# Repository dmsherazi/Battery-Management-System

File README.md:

Battery Management System
-------------------------

This project provides software for monitoring, control and charging of batteries
for a solar powered installation.

The motivation to build this arose from the poor performance, lack of
adequate control, lack of configuration for different battery types, and poor
user interface of commercially available BMS, at least for those reasonably
priced.

The system allows for up to three batteries to be managed separately. This
ensures that failed batteries may be isolated without adversely affecting the
other batteries, as could happen if batteries were connected in parallel. Also
note that if batteries were connected in parallel, the same type and age of
battery must be used, which would necessitate changing all batteries if one were
to fail.

The system also allows for up to two loads so that critical low current loads
may be kept running after high current loads are disconnected in the event
that all batteries fall to critically low charge levels.

The system uses several methods of tracking the State of Charge of each battery,
This is a notoriously difficult parameter to estimate. In a system with three
batteries one may be isolated long enough to allow the terminal voltage to
settle to a level that will allow SoC to be computed accurately.

In the long term it is intended to allow a variety of configurations for
charging and monitoring of batteries:

1. The common three phase charger is provided using PWM to reduce the voltage
   in the absorption phase. In float phase the charger is disconnected until the
   terminal voltage drops to a threshold value. Equalization is not provided.

2. An algorithm based on Interrupted Charge Control (ICC) is also provided to
   place batteries in rest when they have reached the gassing voltage and there
   are other batteries to be charged. This has advantages of:
   (a) better utilization of the charger among the batteries,
   (b) low EMI,
   (c) reduced gas generation.

A wide range of state information is stored on a removable memory, and also
transmitted over a serial link to allow a GUI to display the state accurately
and in detail.

A GUI is provided to allow control and observation of operations. The GUI has
been provided also on a BeagleBone Black card with a LCD touchscreen. This
is suitable for wall installation and draws very low power. For wireless
communications, XBees placed in point-point AT serial mode were successful.

Each of the six interfaces has a hardware overcurrent circuit breaker and low
voltage detector, as well as providing current and voltage measurements.

A central controller based on STM32F103 controls all interfaces and the MOSFET
switches directly. Hardware signals for overcurrent and low voltage are applied
directly to the MOSFET switches for rapid disconnect.

A data processing program is also provided to generate reports of various types
from the recorded performance data.

More information is available on:

http://www.jiggerjuice.info/electronics/projects/solarbms/solarbms-overview.html

(c) K. Sarkies 12/09/2015

TODO

1. Improvement of MOSFET switch drivers to reduce EMI at higher rates.
2. MPPT regulator for the panel.

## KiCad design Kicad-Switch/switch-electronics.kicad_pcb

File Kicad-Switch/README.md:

Battery Management System Switch
--------------------------------

PCB for the MOSFET switch matrix.

Digital circuitry ensures that no two batteries are connected together, which
could cause damage if the state of charge differs significantly.

A diode matrix is used to provide power for the electronics. It ensures that
power is taken from the loads, or from the batteries if the loads are not
connected. This enables the firmware to keep track of the current drawn by
the local electronics.

The MOSFETs are driven by simple BJT-resistor drivers. This results in quite
slow switching speeds. There may be a need for faster switching e.g. high speed
PWM to reduce EMI. In this case the circuit needs to be modified to use better
drivers.

There were several errors in the circuit, which have been corrected but not
tested. The board is to be replaced with the gEDA version.

In the board, load 1 is the central row of switches and the upper power
connector. Load 2 is the lower row of switches and the lower power connector.
This is the reverse of that used in the interconnect board and has been changed
in the gEDA board.

(c) K. Sarkies 26/04/2014

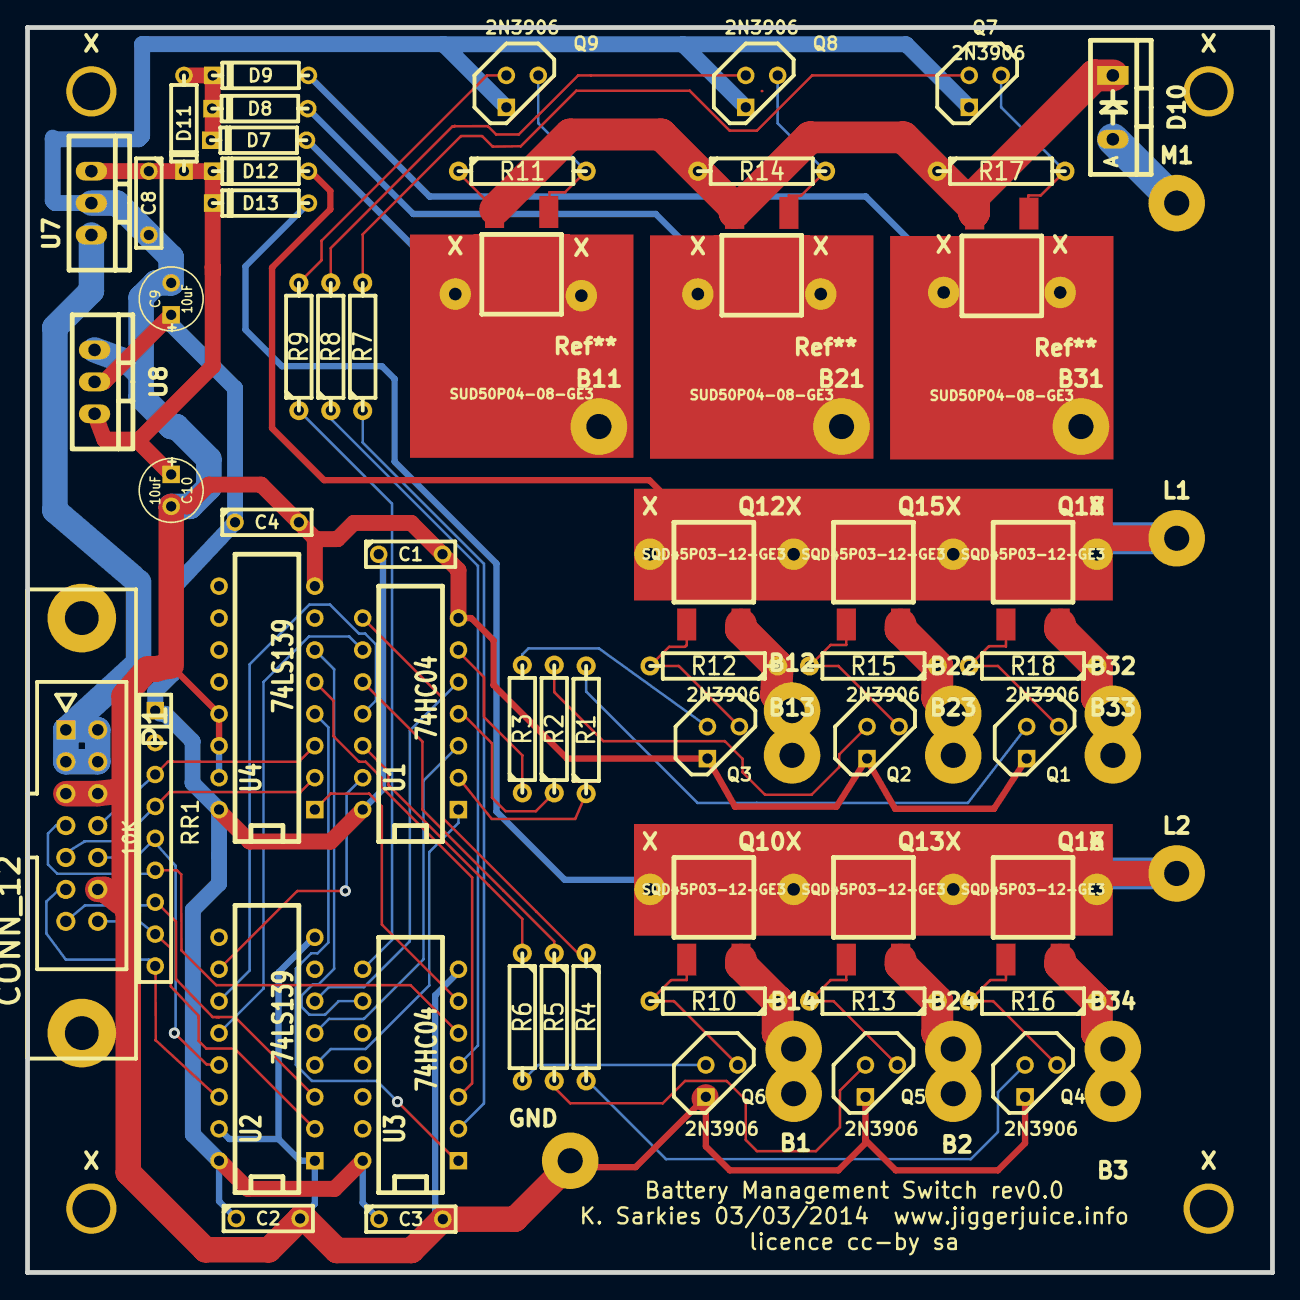
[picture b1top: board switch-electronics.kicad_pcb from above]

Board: 2 copper layers, 99.1 x 99.1 mm, 95 parts (0 on the bottom side), 59 nets.

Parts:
B1, B2, B3, B11, B12, B13, B14, B21, B22, B23, B24, B31, B32, B33, B34: CONN_1; SolderWirePad_single_2mmDrill
C1, C2, C3, C4, C8: 0.1uF; C2
C9, C10: 10uF; C1V5
D7, D8, D9, D11: 1N4701; D3
D10: MBR1645; Diode_TO-220_Vertical
D12, D13: 1N5819; D3
GND: CONN_1; SolderWirePad_single_2mmDrill
L1, L2: CONN_1; SolderWirePad_single_2mmDrill
M1: CONN_1; SolderWirePad_single_2mmDrill
P1: CONN_12; he10-14d
Q1, Q2, Q3, Q4, Q5, Q6, Q7, Q8, Q9: 2N3906; TO92-CBE
Q10, Q12, Q13, Q15, Q16, Q18: SQD45P03-12-GE3; TO252-HS-S
R1, R2, R3, R4, R5, R6, R7, R8, R9: 10K; R4
R10, R11, R12, R13, R14, R15, R16, R17, R18: 1K; R4
RR1: 10K; r_pack8
Ref**: SUD50P04-08-GE3; TO252-HS
Ref**#2, Ref**#3: SUD50P04-08-GE3; TO252-HS
U1, U3: 74HC04; DIP-14__300
U2, U4: 74LS139; DIP-16__300
U7: LM7809CT; TO-220_Neutral123_Vertical
U8: LM1084IT-3.3/NOPB; TO-220_Neutral123_Vertical
X: SolderWirePad_single_2mmDrill
X#2, X#3, X#4: SolderWirePad_single_2mmDrill
X#5, X#6, X#7, X#8, X#9, X#10, X#11, X#12, X#13, X#14, X#15, X#16, X#17, X#18: SolderWirePad_single_1mmDrill

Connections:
9V: P1.11, P1.12, U7.3
B1L1: Q3.C, Q12.G, R12.2
B1L2: Q6.C, Q10.G, R10.2
B1M1: Q9.C, R11.2
B2L1: Q2.C, Q15.G, R15.2
B2L2: Q5.C, Q13.G, R13.2
B2M1: Q8.C, R14.2
B3L1: Q1.C, Q18.G, R18.2
B3L2: Q4.C, Q16.G, R16.2
B3M1: Q7.C, R17.2
GND: C1.2, C2.2, C3.2, C4.2, C8.2, C9.2, C10.2, GND.1, P1.3, P1.9, P1.10, Q1.E, Q2.E, Q3.E, Q4.E, Q5.E, Q6.E, Q7.E, Q8.E, Q9.E, U1.7, U2.1, U2.8, U2.15, U3.7, U4.8, U4.13, U4.14, U4.15, U7.2, U8.1
L1.0: P1.1, RR1.8, U2.3
L1.1: P1.2, RR1.7, U2.2
L2.0: P1.4, RR1.6, U2.13
L2.1: P1.5, RR1.5, U2.14
M1.0: P1.6, RR1.4, U4.3
M1.1: P1.7, RR1.3, U4.2
unnamed: B1.1, R10.1
unnamed: B2.1, R13.1
unnamed: B3.1, R16.1
unnamed: C8.1, C10.1, D11.2, D12.2, D13.2, U7.1, U8.3
unnamed: D7.1, R12.1
unnamed: D8.1, R15.1
unnamed: D9.1, R18.1
unnamed: D10.1, M1.1
unnamed: D10.2, R11.1
unnamed: D7.2, D8.2, D9.2, D11.1
unnamed: D12.1, L1.1
unnamed: D13.1, L2.1
unnamed: Q1.B, R1.2
unnamed: Q2.B, R2.2
unnamed: Q3.B, R3.2
unnamed: Q4.B, R4.2
unnamed: Q5.B, R5.2
unnamed: Q6.B, R6.2
unnamed: Q7.B, R7.2
unnamed: Q8.B, R8.2
unnamed: Q9.B, R9.2
unnamed: R1.1, U1.2
unnamed: R2.1, U1.4
unnamed: R3.1, U1.6
unnamed: R4.1, U1.8
unnamed: R5.1, U1.10
unnamed: R6.1, U1.12
unnamed: R7.1, U3.2
unnamed: R8.1, U3.4
unnamed: R9.1, U3.8
unnamed: U1.1, U2.4
unnamed: U1.3, U2.5
unnamed: U1.5, U2.6
unnamed: U1.9, U2.12
unnamed: U1.11, U2.11
unnamed: U1.13, U2.10
unnamed: U3.1, U4.4
unnamed: U3.3, U4.5
unnamed: U3.6, U4.1
unnamed: U3.9, U4.6
PWM: P1.8, RR1.2, U3.5
VCC: C1.1, C2.1, C3.1, C4.1, C9.1, RR1.1, U1.14, U2.16, U3.14, U4.16, U8.2

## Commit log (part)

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2014-03-14 Initial commit of hardware PCB, firmware, GUI and data processing.
2014-03-14 Add a readme
2014-03-15 Addition of watchdog task for protection and reset of tasks. Change blocking queue and semaphore calls to timeout. Message send functions now dispose of whole message if queue is full. (there is stil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
2014-03-17 Add an option variable to allow a switch avoidance strategy to be used. TODO needs to be added to the GUI
2014-03-21 Set battery charge parameters after a change of battery type
2014-03-21 Add data processing app (preliminary)
2014-03-26 More features for data processing - still not ready Changes to firmware voltage limits to correct corrections back again. Corrections to battery parameter settings Correction to GUI to display newly 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
2014-03-27 Addition of firmware for new PCB version,. Minor corrections to PCB on interface. Removal of extraneous files in all PCB directories
2014-03-30 Data processing. Add "Extract All" to setup a csv file with all data interpreted for loading in a spreadsheet.
2014-04-07 In charger, turn off when voltage drifts too far above limit. If switch avoidance is set, use a bang-bang control. In monitor stop charging if battery in float and above 95% SoC
    In gui, fix capacity displays.
2014-04-07 Fix readme's and remove redundant files
2014-04-08 Better way to incorporate multiple versions of parameters by passing a VERSION define to the program.
2014-04-12 Changes to the monitor. When a battery reaches float state, deallocate the charger. Test all batteries to find a suitable one to charge. If not found, then leave the charger unallocated.
2014-04-15 Charger - change code to stop charging in float phase to a test on all batteries. Monitor - add more decision values Objdic - default battery types to gel for safety. GUI - Add additional indicator f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
2014-04-16 Rework missing battery detection and handling.
2014-04-16 Bug in calibration fixed, now handles the 2 battery case OK.
2014-04-23 Add local footprints directory to interconnect PCB directory
2014-04-25 Layout of gEDA-Switch to replace and correct the Kicad version. Addition of some footprints and symbols and update of footprint for Interconnect (for some reason the solder mask was not opened up on 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
2014-04-25 Add READMEs for the PCB directories.
2014-04-25 Minor changes to remove binary files and make Kicad gerber directory.
2014-04-26 Update all PCBs to correct minor errors. Generate gerbers Need still to check on drill sizes, especially diodes.
2014-05-01 Add pngs of circuit diagrams
2014-05-04 Add =/- to terminal silk screen Add terminal to switch PCB for 9V distribution.
2014-05-06 Adjustments to PCB for manufacture
2014-05-07 Change monitor so that a detected missing battery has its loads removed. GUI configure allow buttons to set a battery as missing as well as not missing.
2014-05-08 Correct some errors. The case of numbats == 1 was not being detected so removed the cryptic addition to the if statement.
2014-05-15 Add feature to scan all currents and print out total AH energies. Total of battery currents gives usage/charge balance. Negative load and charge currents are set to zero - these come from undervoltag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
2014-05-18 Update directory display in file module to show file size. Minor addition to circuit breaker README.
2014-05-24 Fix day error in time module Fix compile warning in measurement module Add in option to GUI to avoid switching in charge algorithm None of these are tested yet.
2014-05-31 Major modification to charger code to incorporate the ICC algorithm as an option to the three phase algorithm.
2014-06-07 Change file system remount to a full initialize as it failed to remount properly.
2014-06-12 Fix missing "break" statement that caused file open problems.
2014-06-12 Introduce ICC algorithm (removed from main charger module). Requires different approach to monitoring. Separate out two charger files and add switch to makefile. ICC CODE IS INCOMPLETE. PRELIMINARY O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
2014-06-13 Repair some docs and also clear status indicators for missing batteries.
2014-06-14 Move generic code from charger-3ph.c to charger-common.inc to be #included As a result the computation of averaged currents and voltages is done on all batteries, even missing ones. Set the Panel swi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
2014-06-16 Add 5V regulator as voltage reference to current monitor. Change offset resistors.
2014-06-20 Revert charger code to just 3 phase to identify problems. Update measurement scaling factors for third amplifier configurations.
2014-07-06 Add tests for battery stuck in absorption phase to monitor firmware Set VERSION=3 to makefile default. New low bias voltage amplifier values.
2014-07-11 Fix bug identifying wrong battery in absorption phase and not charged. Small adjustment to lower threshold for fall out of absorption phase back to bulk.
2014-07-19 Add LICENSE files Update readme to point to web page and reference qextserialport Change location of qextserialport in QT4 pro file Make save file extension more general
2014-08-18 Add capability to split and merge raw data files into day files in data processing utility.
2014-08-30 Correct bugs in ICC. Now use configuration panelSwitchSetting to store preferred battery everywhere. Change monitor to allocate loads according to battery actually charged, keeping the batteryUnderCh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
2014-08-31 Check change of charging status on all batteries, otherwise it may never change.
2014-09-01 Add feature to allow manual reset of SoC from OCV. Add feature to block serial transmission until instructed.
2014-09-02 Add "rest" option to charge state in data processing dump file code.
2014-09-02 ICC algorithm set switches to turn off immediately phase changes to rest or float. Thus avoids overvoltage in the latter part of a slot after the change. Change ICC slot period to 30 seconds.
2014-09-04 Create the IC algorithm. Still to test for current to go to float stage. Add remaining variables to GUI Yet to add these to firmware.
2014-09-04 Completion of code for IC adding change to float phase. Untested.
2014-09-11 Minor corrections to remove reference to CHARGER in makefile, and add charger.h to comms.
2014-09-27 Additional images for switch PCB
2014-09-28 Set monitor task to update SoC whenever the isolated state changes and time in isolation greater than 2 hours.
2014-09-28 File task: Add some additional error checks in attempt to ease recording hangups.
2014-09-28 Fix dumb error in file send command.
2014-10-02 Add first draft of a pulsed charger algorithm
2014-10-02 Further thoughts about pule charge algorithm. Make accumulated off time for checking excessive time in charge.
2014-10-04 Remove reference to libs libqextserialport which calls up an old library in the lib path.
2014-10-10 Update PC and Beaglebone GUIs for new algorithm
2014-10-10 Fix bug that caused SoC to jump to 100% on loaded battery.
2014-10-11 Add an incremental directory listing command to avoid overloading the file interface when the directory listing is long.
2014-10-31 Incremental directory listing in GUI
2014-10-31 Start on moving out common code to support different platforms.
2014-10-31 Add more info about controls to identify charge algorithm in use.
2014-11-09 Update Chan FATfs to a more recent version.
2014-11-10 In pulse charge algorithm, compute accumulated charge over the whole cycle to account for load drain.
2014-11-10 Remove reference to IC algorithm from the GUI
2014-11-11 Remove remaining IC and ICC references and files. Add debug calls to charger-pulse.
2014-11-12 Reset pulse charge algorithm when charger voltage is below 10V.
2014-12-08 chan-fat-stm32-loc3: More improvements to layout and docs. Temporary debug statements to trap FatFs errors arising in physical layer.
2014-12-08 Changed disk_timerproc call in hardware.c to trigger every 10ms instead of 1ms. left over from time when systick was thought to be 10ms. This now extends the wait timeout for SPI data by 10 times. Al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
2014-12-25 Bug fixes in monitor and charging. Move absorption phase decisions to the charger, limiting the time in absorption phase and aborting it when the panel voltage drops out. Fix bug in setting SoC on ch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
2014-12-26 Corrections to charger algorithm
2014-12-27 Charger modify duty cycle on entry to absorption phase to attempt to reduce overshoot. Some name changes.
2014-12-30 Update circuit breaker PCB to reverse regulator and correct voltage amplifier to version 3. Add symbol files.
2015-02-21 Correct some bugs in calling time.h functions.
2015-02-25 interconnect board, added a jumper and pullup resistor so that the current overload signal from the panel can be disabled in hardware.
2015-03-04 Add a feature to allow the ability to connect to a different serial or TCP port with different parameters. Add command line TCP parameters.
2015-03-05 Add features to firmware to allow various battery, tracking and charger parameters to be changed externally.
2015-03-07 Additional GUI features to deal with parameter changes.
2015-03-11 Move a range of defines from the measurement header to the objdic header.
2015-03-11 Remove redundant example file from gui directory
2015-03-11 Add in changing the bulk current limit to the GUI, and fix small error.
2015-03-12 Add a bit more documentation in the form of tooltips to the config window.
2015-03-20 Correct bug in which SoC in GUI wasn't correctly scaled for float to bulk phase change, as well as duty cycle minimum. Add absorption phase suppression to charger in firmware.
2015-03-24 Firmware fix erroneous charging parameter messages.
2015-03-24 GUI fix incorrect filename fields when setting filenames sent from remote.
2015-03-25 Rejig the Beaglebone display and add code to remove the cursed cursor. Change group boxes in main tab to frames. After recalibration the display works but feature size is too small. Need to use a met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
2015-04-03 Add commands in gui to start communications after a serial or TCP connection made.
2015-04-22 Add feature to stop sending messages from the BMS if nothing has been received for 10 seconds. This eases power hungry communication circuits and will work automatically even if the PC were turned of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
2015-05-01 or upgrade to FreeRTOSV8.2.1, this change avoids a compile error (http://www.freertos.org/FreeRTOS_Support_Forum_Archive/October_2014/freertos_FreeRTOS_V812_portmacro.h_missing_binary_operator_before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
2015-05-01 Add a firmware feature to force current calibration to zero for a battery in the event it fails. Add a shutdown button to the BB gui. This relies on a file in /bin that calls the gui and then shuts d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
2015-05-23 GUI Beaglebone. Correct errors in new file creation code.
2015-06-27 Add basic plotting facilities for battery currents and voltages
2015-07-31 Minor change to gui to clean up main screen for radio buttons (they insist on a frame)
2015-08-17 Make the removal of the current zero to be optional. It is best done by the firmware as it takes into account the current drain of the electronics.
2015-08-17 Make the firmware replay with an ident message containing the firmware interface and board versions. The GUI now displays this in teh configuration window, Fix a makefile problem.
2015-09-02 A few very minor changes to different parts of the code - data processing GUI to add a tooltip - firmware to change version back to version 1 - circuit breaker schematic with unknown change
2015-09-12 Adjust temperature compensation for charging, and stop charging above 45C
2015-09-20 Update charger to stop changing to absorption phase if requested, a bit earlier than the previous version (which when to absorption phase for one cycle before detecting the request).

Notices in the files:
Kicad-Switch/switch-electronics.kicad_pcb:
licence cc-by sa
